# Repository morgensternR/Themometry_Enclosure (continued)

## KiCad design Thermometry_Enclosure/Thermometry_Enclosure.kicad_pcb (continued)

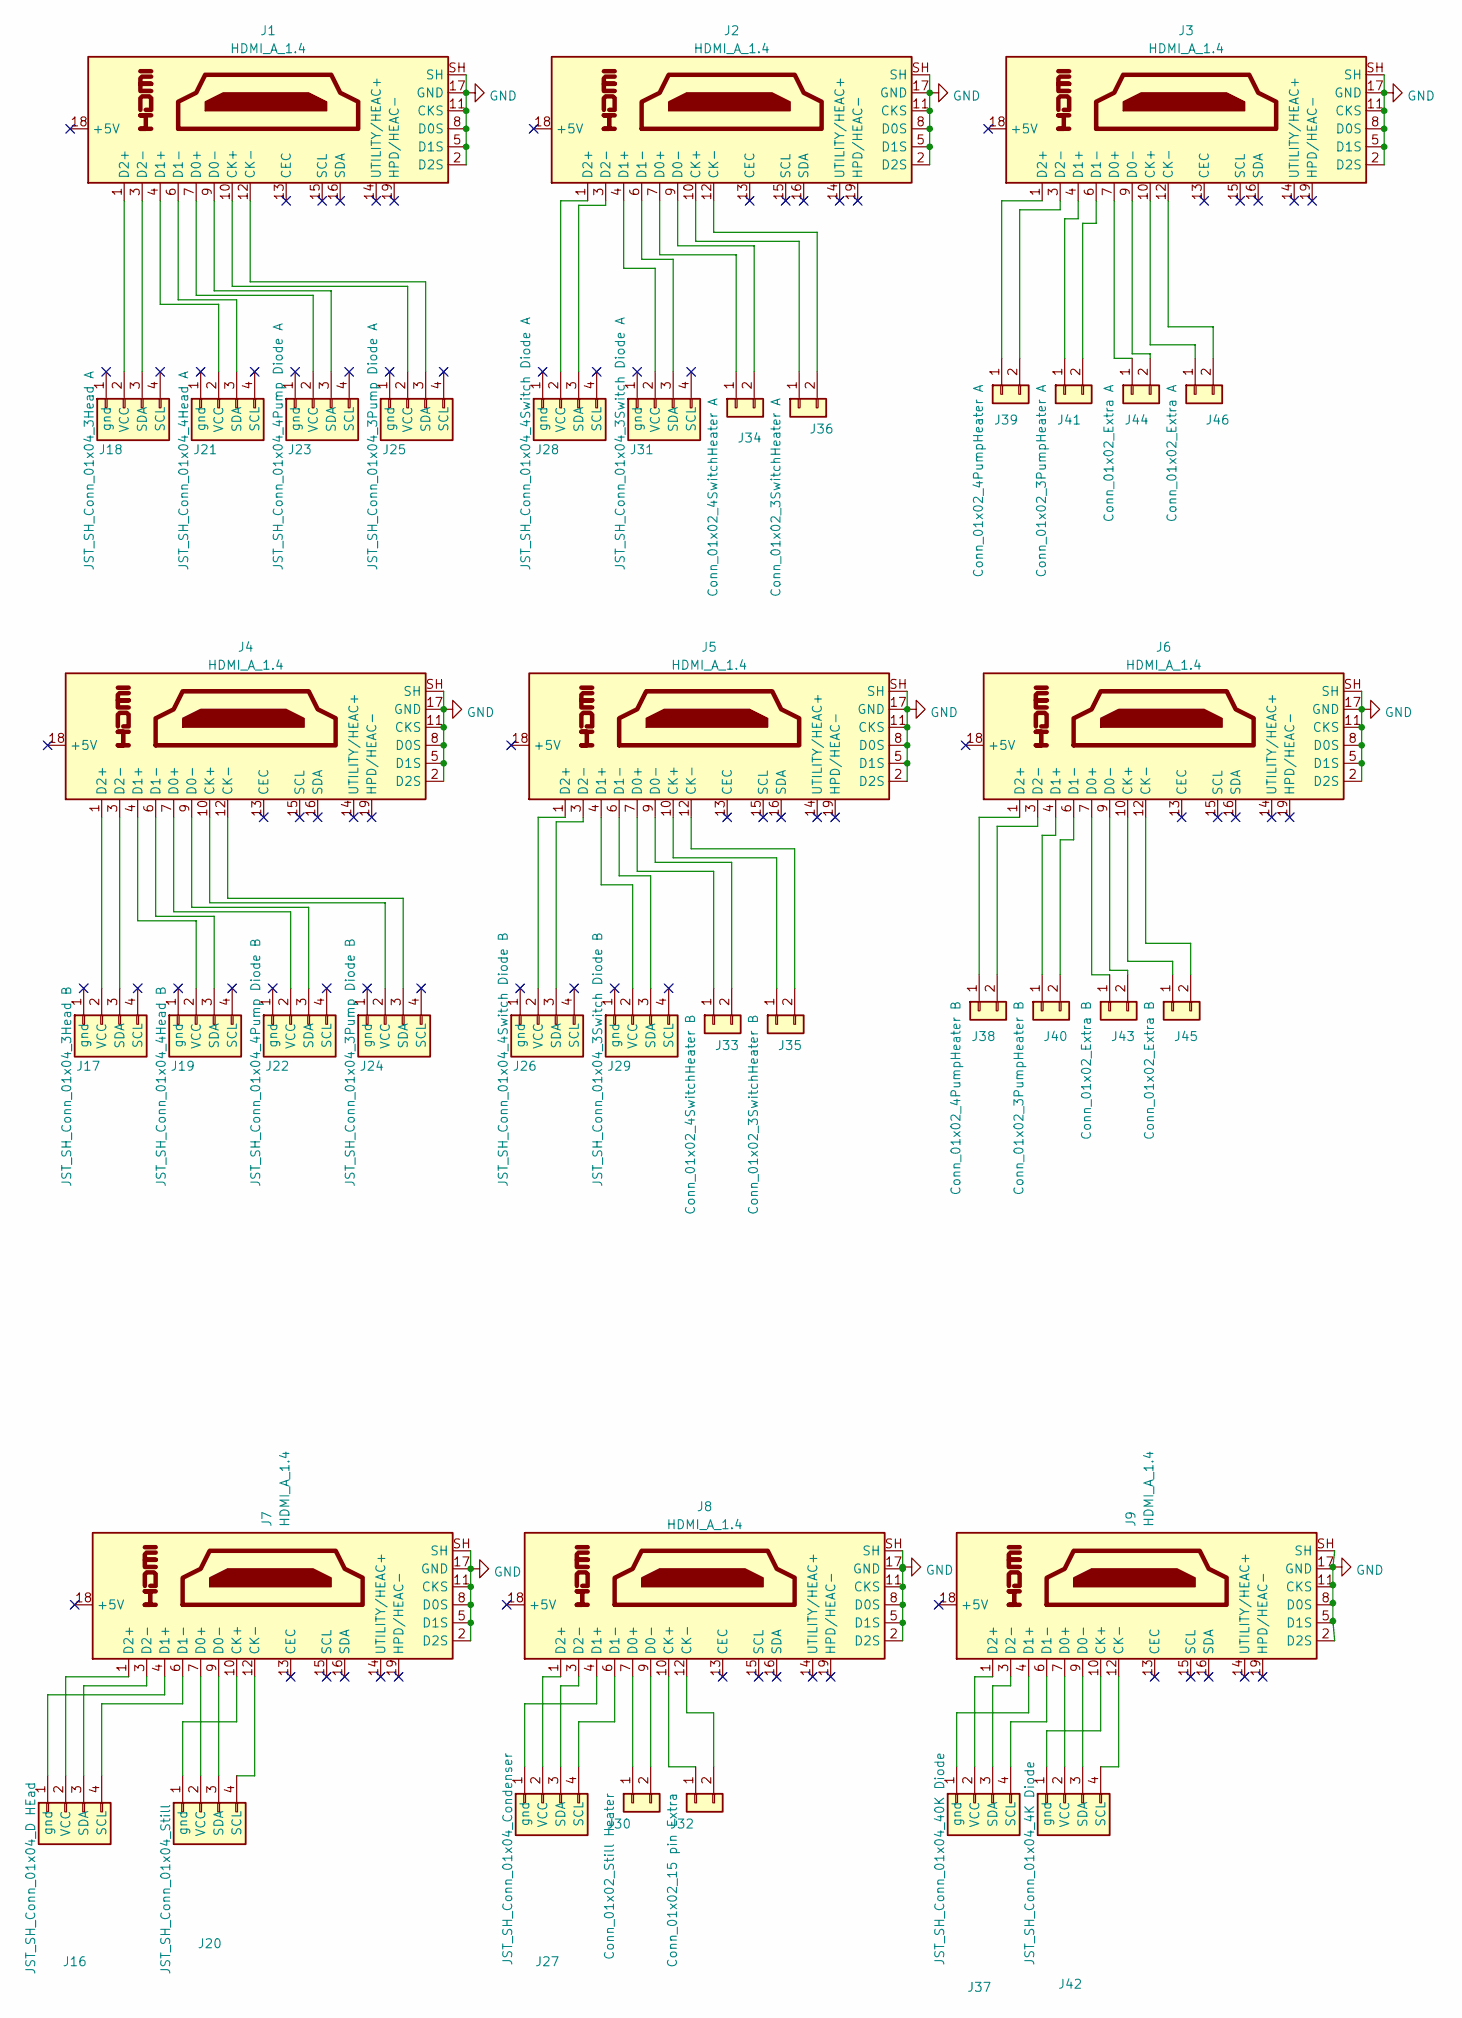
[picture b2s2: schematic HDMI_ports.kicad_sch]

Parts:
J1, J2, J3, J4, J5, J6, J7, J8, J9: HDMI_A_1.4; HDMI-TH_HYC12-HDMIA19-61; LCSC C711354
J16: JST_SH_Conn_01x04_D HEad; JST_SH_BM04B-SRSS-TB_1x04-1MP_P1.00mm_Vertical; MPN A1001WR-S; LCSC C160390
J17: JST_SH_Conn_01x04_3Head B; JST_SH_BM04B-SRSS-TB_1x04-1MP_P1.00mm_Vertical; MPN A1001WR-S; LCSC C160390
J18: JST_SH_Conn_01x04_3Head A; JST_SH_BM04B-SRSS-TB_1x04-1MP_P1.00mm_Vertical; MPN A1001WR-S; LCSC C160390
J19: JST_SH_Conn_01x04_4Head B; JST_SH_BM04B-SRSS-TB_1x04-1MP_P1.00mm_Vertical; MPN A1001WR-S; LCSC C160390
J20: JST_SH_Conn_01x04_Still; JST_SH_BM04B-SRSS-TB_1x04-1MP_P1.00mm_Vertical; MPN A1001WR-S; LCSC C160390
J21: JST_SH_Conn_01x04_4Head A; JST_SH_BM04B-SRSS-TB_1x04-1MP_P1.00mm_Vertical; MPN A1001WR-S; LCSC C160390
J22: JST_SH_Conn_01x04_4Pump Diode B; JST_SH_BM04B-SRSS-TB_1x04-1MP_P1.00mm_Vertical; MPN A1001WR-S; LCSC C160390
J23: JST_SH_Conn_01x04_4Pump Diode A; JST_SH_BM04B-SRSS-TB_1x04-1MP_P1.00mm_Vertical; MPN A1001WR-S; LCSC C160390
J24: JST_SH_Conn_01x04_3Pump Diode B; JST_SH_BM04B-SRSS-TB_1x04-1MP_P1.00mm_Vertical; MPN A1001WR-S; LCSC C160390
J25: JST_SH_Conn_01x04_3Pump Diode A; JST_SH_BM04B-SRSS-TB_1x04-1MP_P1.00mm_Vertical; MPN A1001WR-S; LCSC C160390
J26: JST_SH_Conn_01x04_4Switch Diode B; JST_SH_BM04B-SRSS-TB_1x04-1MP_P1.00mm_Vertical; MPN A1001WR-S; LCSC C160390
J27: JST_SH_Conn_01x04_Condenser; JST_SH_BM04B-SRSS-TB_1x04-1MP_P1.00mm_Vertical; MPN A1001WR-S; LCSC C160390
J28: JST_SH_Conn_01x04_4Switch Diode A; JST_SH_BM04B-SRSS-TB_1x04-1MP_P1.00mm_Vertical; MPN A1001WR-S; LCSC C160390
J29: JST_SH_Conn_01x04_3Switch Diode B; JST_SH_BM04B-SRSS-TB_1x04-1MP_P1.00mm_Vertical; MPN A1001WR-S; LCSC C160390
J30: Conn_01x02_Still Heater; JST_PH_B2B-PH-K_1x02_P2.00mm_Vertical; LCSC C2683610
J31: JST_SH_Conn_01x04_3Switch Diode A; JST_SH_BM04B-SRSS-TB_1x04-1MP_P1.00mm_Vertical; MPN A1001WR-S; LCSC C160390
J32: Conn_01x02_15 pin Extra; JST_PH_B2B-PH-K_1x02_P2.00mm_Vertical; LCSC C2683610
J33: Conn_01x02_4SwitchHeater B; JST_PH_B2B-PH-K_1x02_P2.00mm_Vertical; LCSC C2683610
J34: Conn_01x02_4SwitchHeater A; JST_PH_B2B-PH-K_1x02_P2.00mm_Vertical; LCSC C2683610
J35: Conn_01x02_3SwitchHeater B; JST_PH_B2B-PH-K_1x02_P2.00mm_Vertical; LCSC C2683610
J36: Conn_01x02_3SwitchHeater A; JST_PH_B2B-PH-K_1x02_P2.00mm_Vertical; LCSC C2683610
J37: JST_SH_Conn_01x04_40K Diode; JST_SH_BM04B-SRSS-TB_1x04-1MP_P1.00mm_Vertical; MPN A1001WR-S; LCSC C160390
J38: Conn_01x02_4PumpHeater B; JST_PH_B2B-PH-K_1x02_P2.00mm_Vertical; LCSC C2683610
J39: Conn_01x02_4PumpHeater A; JST_PH_B2B-PH-K_1x02_P2.00mm_Vertical; LCSC C2683610
J40: Conn_01x02_3PumpHeater B; JST_PH_B2B-PH-K_1x02_P2.00mm_Vertical; LCSC C2683610
J41: Conn_01x02_3PumpHeater A; JST_PH_B2B-PH-K_1x02_P2.00mm_Vertical; LCSC C2683610
J42: JST_SH_Conn_01x04_4K Diode; JST_SH_BM04B-SRSS-TB_1x04-1MP_P1.00mm_Vertical; MPN A1001WR-S; LCSC C160390
J43, J45: Conn_01x02_Extra B; JST_PH_B2B-PH-K_1x02_P2.00mm_Vertical; LCSC C2683610
J44, J46: Conn_01x02_Extra A; JST_PH_B2B-PH-K_1x02_P2.00mm_Vertical; LCSC C2683610

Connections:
GND: J1.2 (D2S), J1.5 (D1S), J1.8 (D0S), J1.11 (CKS), J1.17 (GND), J1.SH, J2.2 (D2S), J2.5 (D1S), J2.8 (D0S), J2.11 (CKS), J2.17 (GND), J2.SH, J3.2 (D2S), J3.5 (D1S), J3.8 (D0S), J3.11 (CKS), J3.17 (GND), J3.SH, J4.2 (D2S), J4.5 (D1S), J4.8 (D0S), J4.11 (CKS), J4.17 (GND), J4.SH, J5.2 (D2S), J5.5 (D1S), J5.8 (D0S), J5.11 (CKS), J5.17 (GND), J5.SH, J6.2 (D2S), J6.5 (D1S), J6.8 (D0S), J6.11 (CKS), J6.17 (GND), J6.SH, J7.2 (D2S), J7.5 (D1S), J7.8 (D0S), J7.11 (CKS), J7.17 (GND), J7.SH, J8.2 (D2S), J8.5 (D1S), J8.8 (D0S), J8.11 (CKS), J8.17 (GND), J8.SH, J9.2 (D2S), J9.5 (D1S), J9.8 (D0S), J9.11 (CKS), J9.17 (GND), J9.SH; also elsewhere on the board
unnamed: J1.1 (D2+), J18.2 (VCC)
unnamed: J1.3 (D2-), J18.3 (SDA)
unnamed: J1.4 (D1+), J21.2 (VCC)
unnamed: J1.6 (D1-), J21.3 (SDA)
unnamed: J1.7 (D0+), J23.2 (VCC)
unnamed: J1.9 (D0-), J23.3 (SDA)
unnamed: J1.10 (CK+), J25.2 (VCC)
unnamed: J1.12 (CK-), J25.3 (SDA)
unnamed: J2.1 (D2+), J28.2 (VCC)
unnamed: J2.3 (D2-), J28.3 (SDA)
unnamed: J2.4 (D1+), J31.2 (VCC)
unnamed: J2.6 (D1-), J31.3 (SDA)
unnamed: J2.7 (D0+), J34.1
unnamed: J2.9 (D0-), J34.2
unnamed: J2.10 (CK+), J36.1
unnamed: J2.12 (CK-), J36.2
unnamed: J3.1 (D2+), J39.1
unnamed: J3.3 (D2-), J39.2
unnamed: J3.4 (D1+), J41.1
unnamed: J3.6 (D1-), J41.2
unnamed: J3.7 (D0+), J44.1
unnamed: J3.9 (D0-), J44.2
unnamed: J3.10 (CK+), J46.1
unnamed: J3.12 (CK-), J46.2
unnamed: J7.4 (D1+), J16.1 (gnd)
unnamed: J7.1 (D2+), J16.2 (VCC)
unnamed: J7.3 (D2-), J16.3 (SDA)
unnamed: J7.6 (D1-), J16.4 (SCL)
unnamed: J4.1 (D2+), J17.2 (VCC)
unnamed: J4.3 (D2-), J17.3 (SDA)
unnamed: J4.4 (D1+), J19.2 (VCC)
unnamed: J4.6 (D1-), J19.3 (SDA)
unnamed: J7.10 (CK+), J20.1 (gnd)
unnamed: J7.7 (D0+), J20.2 (VCC)
unnamed: J7.9 (D0-), J20.3 (SDA)
unnamed: J7.12 (CK-), J20.4 (SCL)
unnamed: J4.7 (D0+), J22.2 (VCC)
unnamed: J4.9 (D0-), J22.3 (SDA)
unnamed: J4.10 (CK+), J24.2 (VCC)
unnamed: J4.12 (CK-), J24.3 (SDA)
unnamed: J5.1 (D2+), J26.2 (VCC)
unnamed: J5.3 (D2-), J26.3 (SDA)
unnamed: J8.4 (D1+), J27.1 (gnd)
unnamed: J8.1 (D2+), J27.2 (VCC)
unnamed: J8.3 (D2-), J27.3 (SDA)
unnamed: J8.6 (D1-), J27.4 (SCL)
unnamed: J5.4 (D1+), J29.2 (VCC)
unnamed: J5.6 (D1-), J29.3 (SDA)
unnamed: J8.7 (D0+), J30.1
unnamed: J8.9 (D0-), J30.2
unnamed: J8.10 (CK+), J32.1
unnamed: J8.12 (CK-), J32.2
unnamed: J5.7 (D0+), J33.1
unnamed: J5.9 (D0-), J33.2
unnamed: J5.10 (CK+), J35.1
unnamed: J5.12 (CK-), J35.2
unnamed: J9.4 (D1+), J37.1 (gnd)
unnamed: J9.1 (D2+), J37.2 (VCC)
unnamed: J9.3 (D2-), J37.3 (SDA)
unnamed: J9.6 (D1-), J37.4 (SCL)
unnamed: J6.1 (D2+), J38.1
unnamed: J6.3 (D2-), J38.2
unnamed: J6.4 (D1+), J40.1
unnamed: J6.6 (D1-), J40.2
unnamed: J9.10 (CK+), J42.1 (gnd)
unnamed: J9.7 (D0+), J42.2 (VCC)
unnamed: J9.9 (D0-), J42.3 (SDA)
unnamed: J9.12 (CK-), J42.4 (SCL)
unnamed: J6.7 (D0+), J43.1
unnamed: J6.9 (D0-), J43.2
unnamed: J6.10 (CK+), J45.1
unnamed: J6.12 (CK-), J45.2

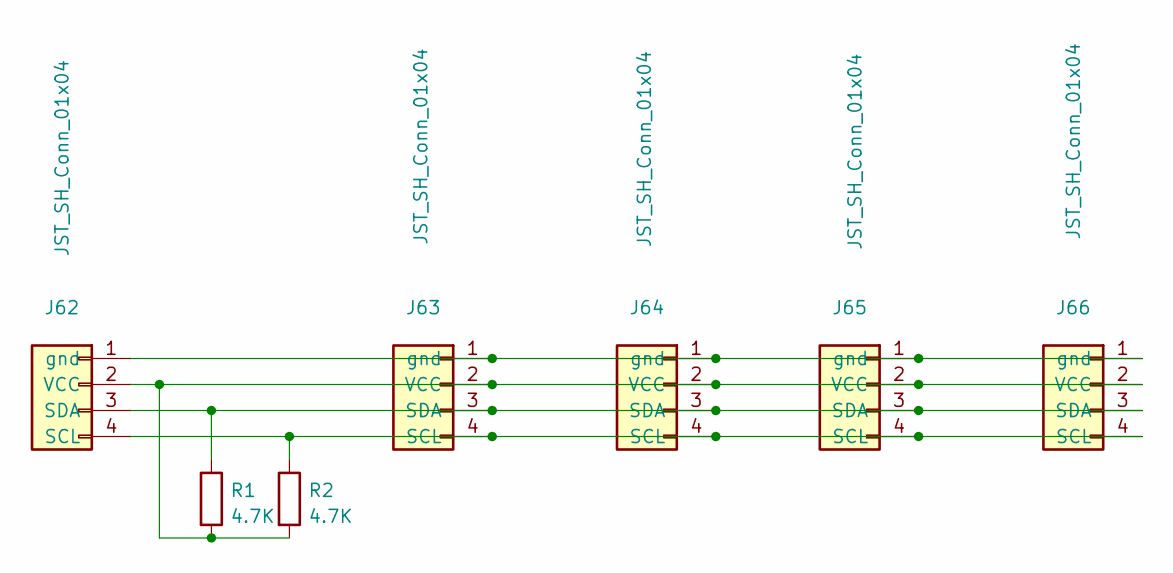
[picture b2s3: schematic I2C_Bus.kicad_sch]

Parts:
J62, J63, J64, J65, J66: JST_SH_Conn_01x04; JST_SH_BM04B-SRSS-TB_1x04-1MP_P1.00mm_Vertical; LCSC C160390
R1, R2: 4.7K; R_0603_1608Metric_Pad0.98x0.95mm_HandSolder; LCSC C99782

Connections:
unnamed: J62.1 (gnd), J63.1 (gnd), J64.1 (gnd), J65.1 (gnd), J66.1 (gnd)
unnamed: J62.2 (VCC), J63.2 (VCC), J64.2 (VCC), J65.2 (VCC), J66.2 (VCC), R1.2, R2.2
unnamed: J62.3 (SDA), J63.3 (SDA), J64.3 (SDA), J65.3 (SDA), J66.3 (SDA), R1.1
unnamed: J62.4 (SCL), J63.4 (SCL), J64.4 (SCL), J65.4 (SCL), J66.4 (SCL), R2.1

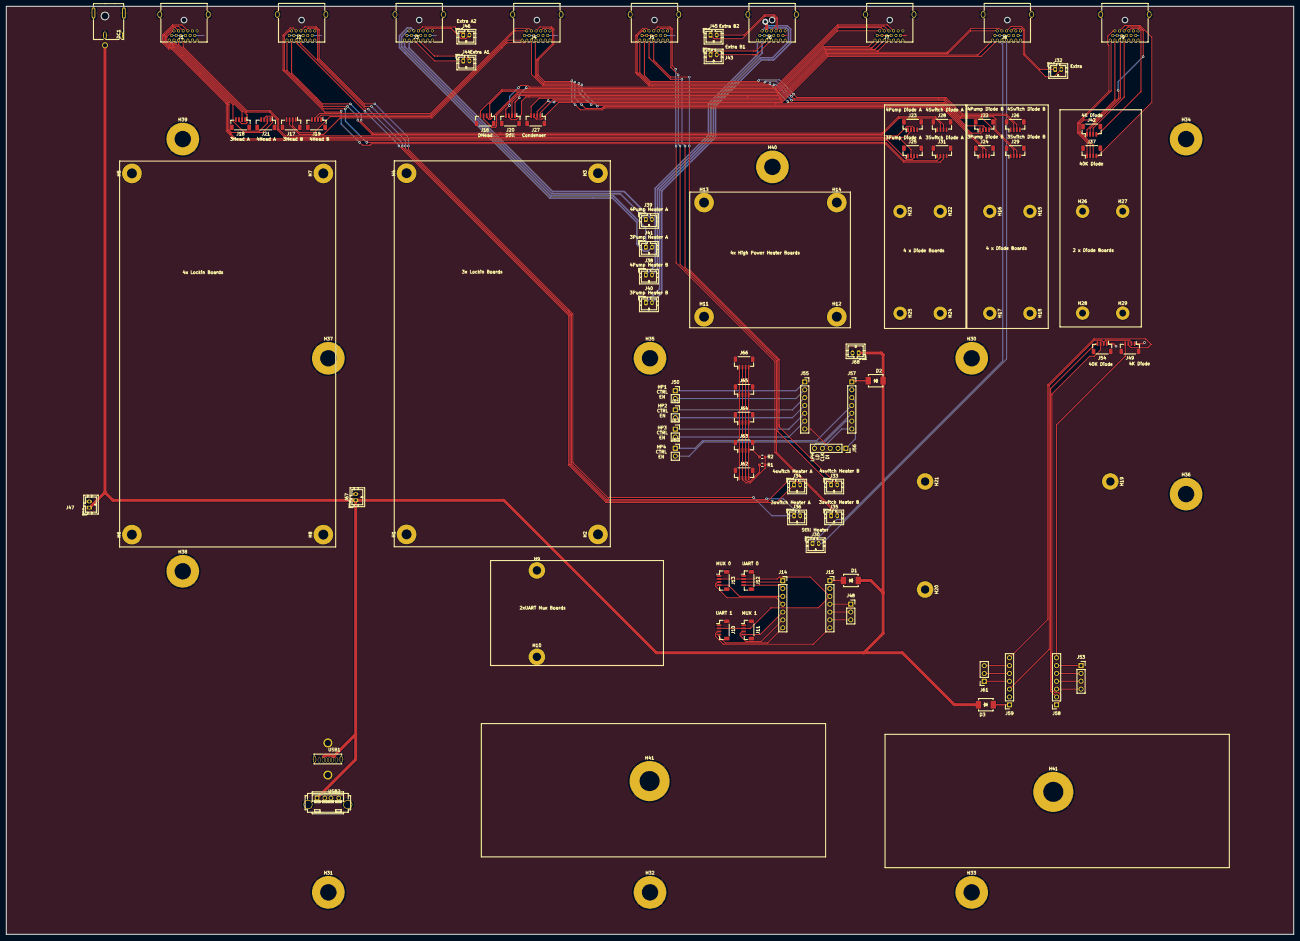
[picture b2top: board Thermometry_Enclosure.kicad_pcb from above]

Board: 2 copper layers, 417.0 x 300.6 mm, 118 parts (0 on the bottom side), 117 nets.

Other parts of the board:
H41#2: MountingHole_Pad; MountingHole_6.5mm_Pad

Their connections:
GND: H41#2.1; also elsewhere on the board

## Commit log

2023-06-21 Removed files unrelated
2023-06-21 Create LICENSE
